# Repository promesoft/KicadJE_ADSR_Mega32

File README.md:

# KicadJE_ADSR_Mega32
Initial ATMega32 board (EU-5 ADSR32)

Second PT2399 reverb (EU-4 Reverb)

Third VCO - based on Format VCO (VCO3)

# Purpose
1 - try out ATMega 32 for digital applications with more IO

2 - PT2399 2nd revision

3 - Formant VCO modification 3rd rev

# Status - delivered
## Initial 
| Stage  | Detail | Status |
| ------------- | ------------- | ------------- |
| create material  | sch/pcb | OK  |
| | gerber | OK |
| production  |   | OK |
|  | produced | OK |
|  | delivered | OK |

## Preliminary validation
| Test  | Detail | Status |
| ------------- | ------------- | ------------- |
| Initial Inspection | | OK |
| Initial Technical Test | ADSR | ICSP:ok - Serial: no success - LED: OK - POT:no success|
| Initial Technical Test | Reverb | OK |
| Initial Technical Test | VCO3 | OK |
| Initial Product Test | ADSR | ADC not working due to GND conn to Aref |
| Initial Product Test | Reverb | Works nicely (tested with 5V from 16pin Doepfer|
| Initial Product Test | VCO3 | Working - output and "sine" - Square not working - UMX1 works nicely as CV - FM works - LFO works - POT's reversed... |

## Secondary validation
| Test  | Detail | Status |
| ------------- | ------------- |------------- |
| Product Test |  |  |
| Product Test |  |  |
| Product Test | VCO | Square not working|
| Quality | | |
| Quality | | |
| Quality | VCO3 | Range from 20Hz |
| Long Term Product Test |  |  |
| Long Term Product Test |  |  |
| Long Term Product Test |  |  |
| Power Draw |  | 
| Power Draw |  | 
| Power Draw | VCO3 | +5V 1mA, +12V 7mA, -12V 6mA 

## Errata
### Errata - VCO3
1 - ALL pots are reversed
### Errata - ADSR Mega32
1 - ADC not working due to GND conn to Aref - fix by bending leg so it does not get soldered

## Issues and Notes
### VCO 3
1 - C104 needs to be bigger (tried w 20uf that worked nicely)

2 - Square circuit not working

3 - Unsure of trigger feature

4 - ALL pots are reversed

5 - Consider adding LED

# Pictures

## VCO3

## Reverb

# Inspiration from 
https://github.com/promesoft/KicadJE_EffectsUnit1

https://github.com/promesoft/ArduinoJE_ADSR

https://github.com/promesoft/KicadFormantVCO

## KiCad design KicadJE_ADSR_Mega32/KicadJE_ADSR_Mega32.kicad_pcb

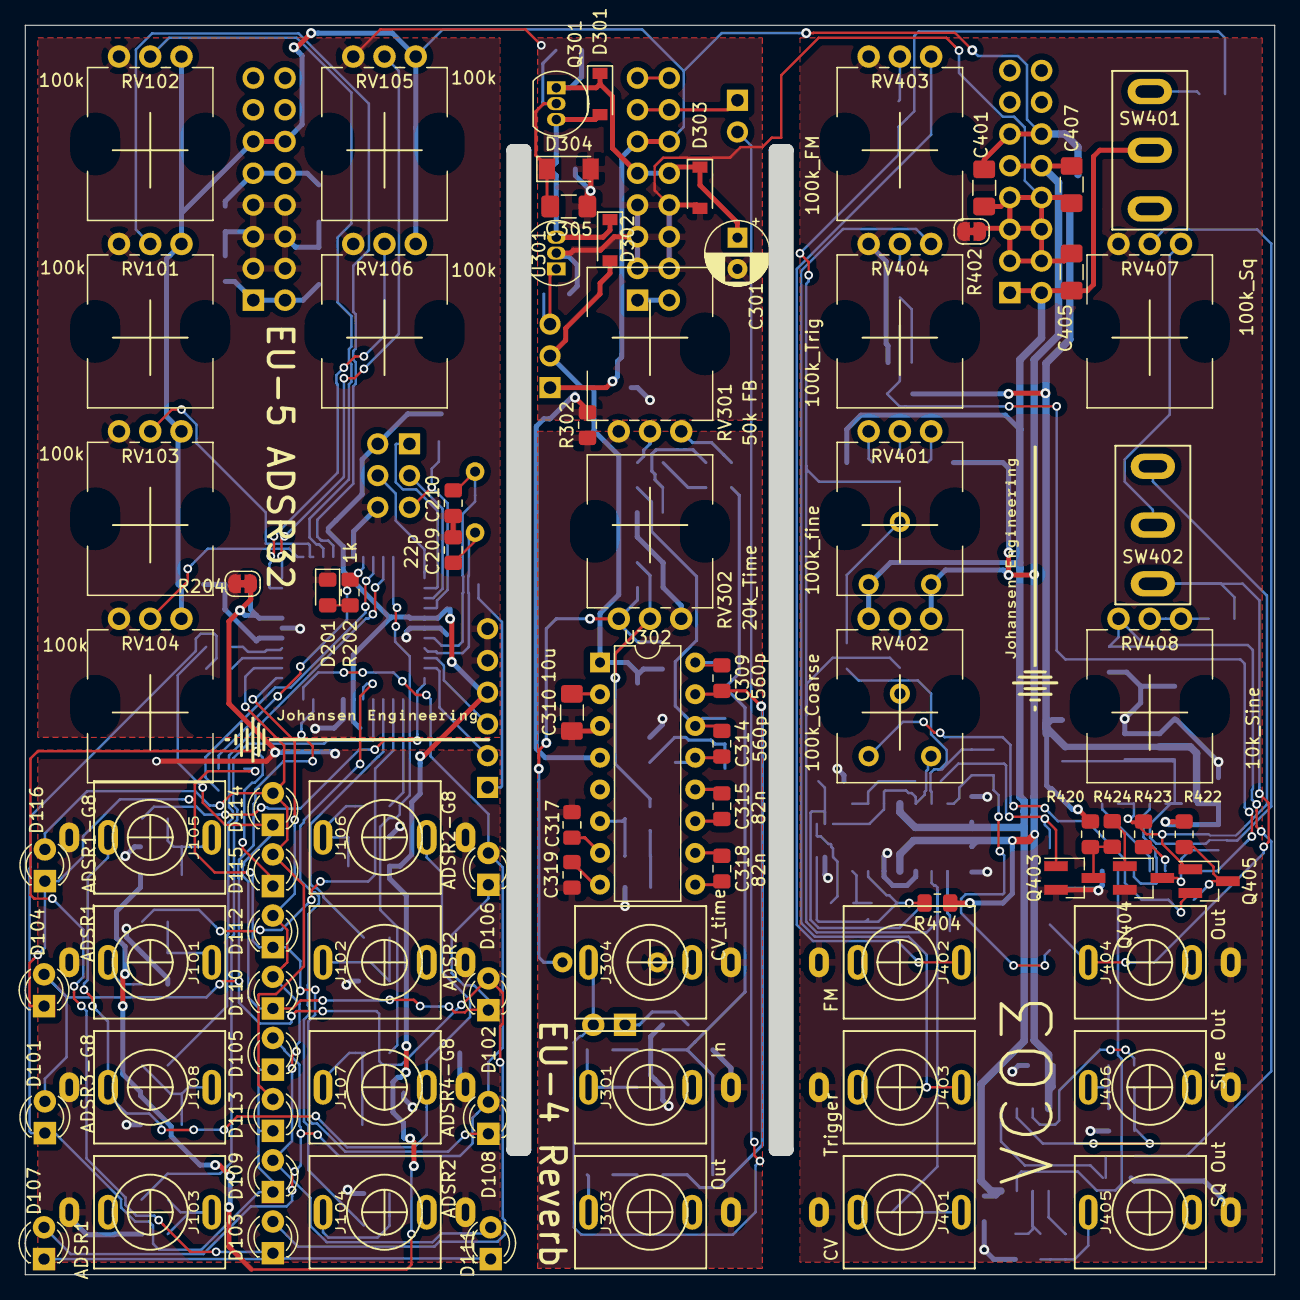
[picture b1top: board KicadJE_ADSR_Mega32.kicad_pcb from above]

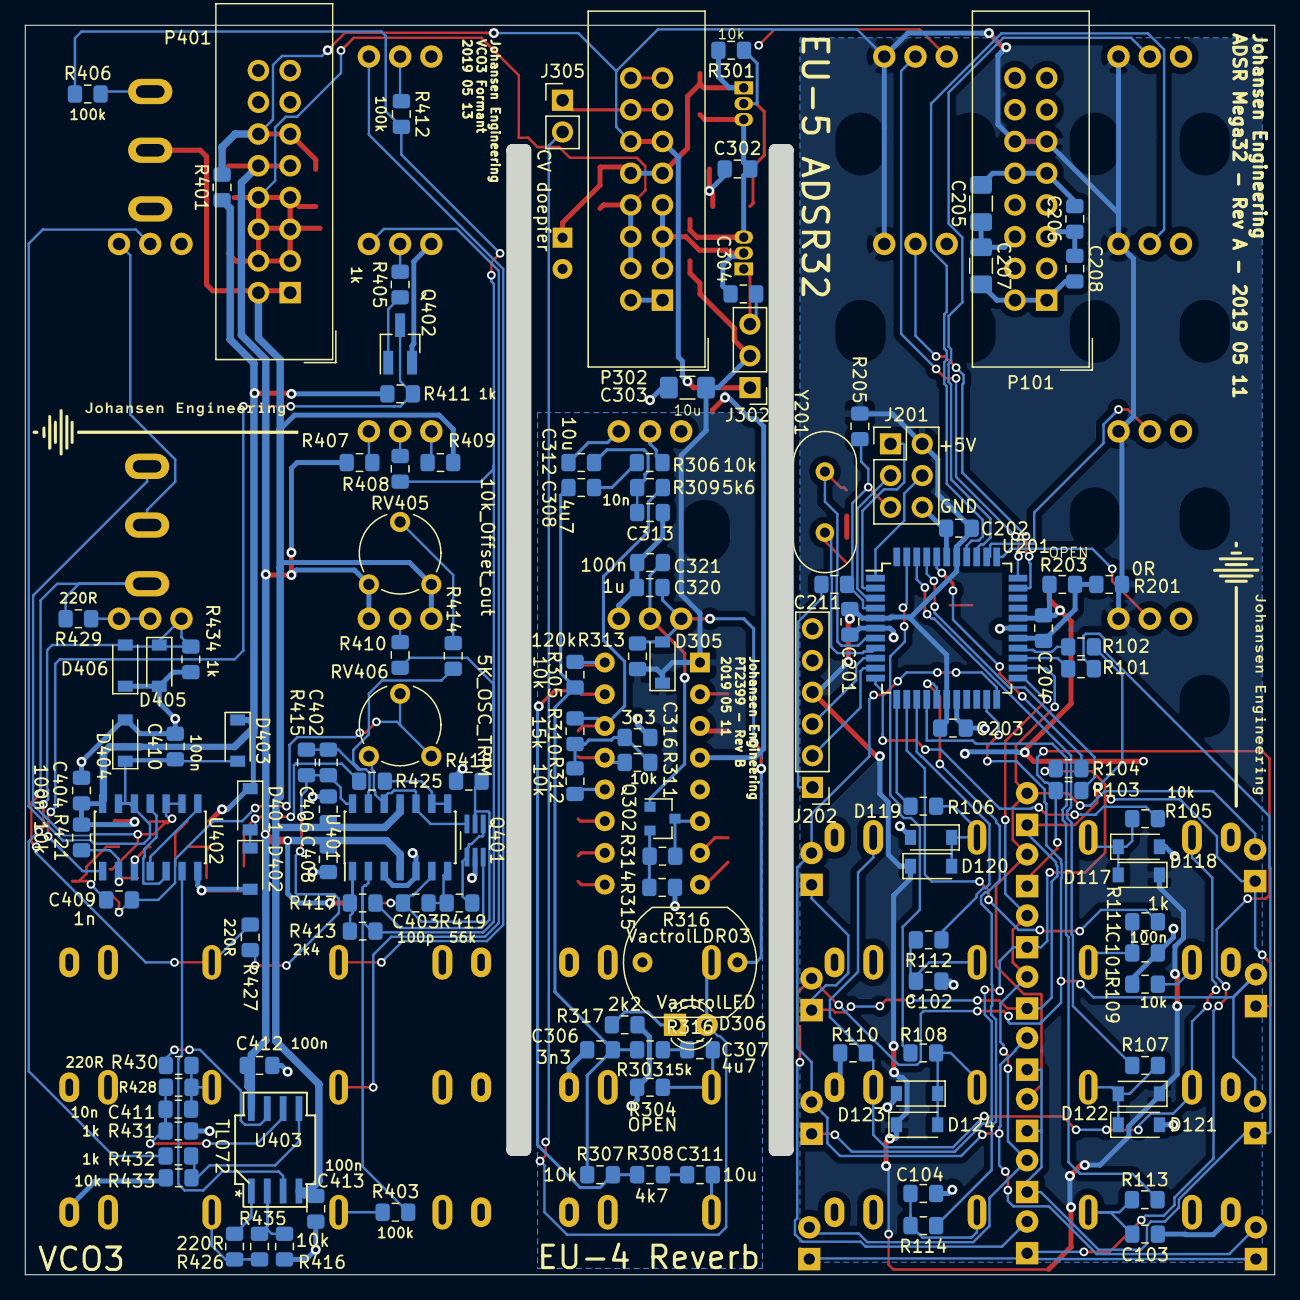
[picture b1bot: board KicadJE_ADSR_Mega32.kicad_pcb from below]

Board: 2 copper layers, 100.0 x 100.0 mm, 213 parts (130 on the bottom side), 132 nets.

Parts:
C101, C103, C201, C202, C203, C204, C206, C208, C211, C302, C304, C317, C319, C321, C404, C406, C408, C410, C412, C413: 100n; C_0805_2012Metric_Pad1.15x1.40mm_HandSolder
C102, C104, C320: 1u; C_0805_2012Metric_Pad1.15x1.40mm_HandSolder
C205, C207: 100n; C_1206_3216Metric_Pad1.42x1.75mm_HandSolder
C209, C210: 22p; C_0805_2012Metric_Pad1.15x1.40mm_HandSolder
C301: 100uF 16v; CP_Radial_D5.0mm_P2.50mm
C303, C305, C310: 10u; C_1206_3216Metric_Pad1.42x1.75mm_HandSolder
C306, C316: 3n3; C_0805_2012Metric_Pad1.15x1.40mm_HandSolder
C307, C308: 4u7; C_0805_2012Metric_Pad1.15x1.40mm_HandSolder
C309, C314: 560p; C_0805_2012Metric_Pad1.15x1.40mm_HandSolder
C311, C312: 10u; C_0805_2012Metric_Pad1.15x1.40mm_HandSolder
C313, C411: 10n; C_0805_2012Metric_Pad1.15x1.40mm_HandSolder
C315, C318: 82n; C_0805_2012Metric_Pad1.15x1.40mm_HandSolder
C401, C405, C407: 1u; C_1206_3216Metric_Pad1.42x1.75mm_HandSolder
C402: 12p; C_0805_2012Metric_Pad1.15x1.40mm_HandSolder
C403: 100p; C_0805_2012Metric_Pad1.15x1.40mm_HandSolder
C409: 1n; C_0805_2012Metric_Pad1.15x1.40mm_HandSolder
D101, D102, D103, D104, D105, D106, D107, D108, D109, D110, D111, D112, D113, D114, D115, D116: LED; LED_D3.0mm
D117, D118, D119, D120, D121, D122, D123, D124, D301, D302, D303, D305: 1N1007; D_SOD-123
D201: LED; LED_0805_2012Metric_Pad1.15x1.40mm_HandSolder
D304: 7v5; D_MiniMELF
D306: VactrolLED; LED_D3.0mm
D401, D402, D403, D404, D405, D406: 1N4148; D_SOD-123
J101, J103: ADSR1; PJ301SM
J102, J104: ADSR2; PJ301SM
J105: ADSR1-G8; PJ301SM
J106: ADSR2-G8; PJ301SM
J107: ADSR4-G8; PJ301SM
J108: ADSR3-G8; PJ301SM
J201: AVR-ISP-6; PinHeader_2x03_P2.54mm_Vertical
J202: UART; PinHeader_1x06_P2.54mm_Vertical
J301: In; PJ301SM
J302: +5V reg/doepfer; PinHeader_1x03_P2.54mm_Vertical
J303, J404: Out; PJ301SM
J304: CV_time; PJ301SM
J305: CV doepfer; PinHeader_1x02_P2.54mm_Vertical
J401: CV; PJ301SM
J402: FM; PJ301SM
J403: Trigger; PJ301SM
J405: SQ Out; PJ301SM
J406: Sine Out; PJ301SM
P101, P302, P401: Doepfer_Power_16pin; IDC-Header_2x08_Pitch2.54mm_Straight
Q301: BC337; TO-92_Inline
Q302: PZT2222A; SOT-23
Q401: UMX1N; SOT-363_SC-70-6_Handsoldering
Q402, Q403, Q404, Q405: MMBT2222A; SOT-23_Handsoldering
R101, R103, R414: 100R; R_0805_2012Metric_Pad1.15x1.40mm_HandSolder
R102, R104: 100r; R_0805_2012Metric_Pad1.15x1.40mm_HandSolder
R105, R106, R107, R108, R109, R110, R112, R114, R205, R301, R305, R306, R307, R311, R312, R416, R420, R421, R422, R428, R433, R435: 10k; R_0805_2012Metric_Pad1.15x1.40mm_HandSolder
R111, R113, R202, R405, R411, R424, R425, R431, R432, R434: 1k; R_0805_2012Metric_Pad1.15x1.40mm_HandSolder
R201, R302, R401: 0R; R_0805_2012Metric_Pad1.15x1.40mm_HandSolder
R203, R304: OPEN; R_0805_2012Metric_Pad1.15x1.40mm_HandSolder
R204, R402: 0R; SolderJumper-2_P1.3mm_Bridged_RoundedPad1.0x1.5mm
R303, R310: 15k; R_0805_2012Metric_Pad1.15x1.40mm_HandSolder
R308, R415: 4k7; R_0805_2012Metric_Pad1.15x1.40mm_HandSolder
R309: 5k6; R_0805_2012Metric_Pad1.15x1.40mm_HandSolder
R313: 120k; R_0805_2012Metric_Pad1.15x1.40mm_HandSolder
R314: 22k; R_0805_2012Metric_Pad1.15x1.40mm_HandSolder
R315: 150R; R_0805_2012Metric_Pad1.15x1.40mm_HandSolder
R316: VactrolLDR03; R_LDR_10x8.5mm_P7.6mm_Vertical
R317: 2k2; R_0805_2012Metric_Pad1.15x1.40mm_HandSolder
R403, R406, R407, R408, R409, R410, R412: 100k; R_0805_2012Metric_Pad1.15x1.40mm_HandSolder
R404: 1M; R_0805_2012Metric_Pad1.15x1.40mm_HandSolder
R413: 2k4; R_0805_2012Metric_Pad1.15x1.40mm_HandSolder
R417: 82R; R_0805_2012Metric_Pad1.15x1.40mm_HandSolder
R418: 910R; R_0805_2012Metric_Pad1.15x1.40mm_HandSolder
R419: 56k; R_0805_2012Metric_Pad1.15x1.40mm_HandSolder
R423, R426, R427, R429, R430: 220R; R_0805_2012Metric_Pad1.15x1.40mm_HandSolder
RV101, RV102, RV103, RV104, RV105, RV106: 100k; Potentiometer_China_RK09_Single_Vertical_AJ
RV301: 50k FB; Potentiometer_China_RK09_Single_Vertical_AJ
RV302: 20k_Time; Potentiometer_China_RK09_Single_Vertical_AJ
RV401: 100k_fine; Potentiometer_China_RK09_Single_Vertical_AJ
RV402: 100k_Coarse; Potentiometer_China_RK09_Single_Vertical_AJ
RV403: 100k_FM; Potentiometer_China_RK09_Single_Vertical_AJ
RV404: 100k_Trig; Potentiometer_China_RK09_Single_Vertical_AJ
RV405: 10k_Offset_out; Potentiometer_Piher_PT-6-V_Vertical
RV406: 5K_OSC_TRIM; Potentiometer_Piher_PT-6-V_Vertical
RV407: 100k_Sq; Potentiometer_China_RK09_Single_Vertical_AJ
RV408: 10k_Sine; Potentiometer_China_RK09_Single_Vertical_AJ
SW401: LFO; SP1MS1
SW402: SQ_Source; SP1MS1
U201: ATmega32A-AU; TQFP-44_10x10mm_P0.8mm
U301: L78L05_TO92; TO-92_Inline
U302: PT2399; DIP-16_W7.62mm
U401: TL074; SOIC-14_3.9x8.7mm_P1.27mm
U402: 74HC00; SOIC-14_3.9x8.7mm_P1.27mm
U403: TL072; AJ_SO-8_5.3x6.2mm_P1.27mm
Y201: 16MHz; Crystal_HC49-U_Vertical

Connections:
0_LED: R104.1, R202.2, U201.40
1: R103.1, U201.41
2_INT2: R107.1, U201.42
3_PWM: R108.1, U201.43
5Vreg: C304.2, J302.3, U301.1
5_MOSI: J201.4, U201.1
6_MISO: J201.1, U201.2
7_SCK: J201.3, U201.3
8_Rx: J202.3, U201.9
9_Tx: J202.2, U201.10
10_INT0: R105.1, U201.11
11_INT1: R106.1, U201.12
12_PWM: R111.1, U201.13
13_PWM: R112.1, U201.14
14_PWM: R113.1, U201.15
15_PWM: R114.1, U201.16
18: D101.2, D102.2, D103.2, D104.2, U201.21
19: D105.2, D106.2, D107.2, D108.2, U201.22
20: D109.2, D110.2, D111.2, D112.2, U201.23
21: D113.2, D114.2, D115.2, D116.2, U201.24
22: R101.1, U201.25
23: R102.1, U201.26
24_A0: RV101.2, U201.37
25_A1: RV102.2, U201.36
26_A2: RV103.2, U201.35
27_A3: RV104.2, U201.34
28_A4: RV105.2, U201.33
29_A5: RV106.2, U201.32
+5V: C201.2, C202.2, C203.2, C401.2, D117.1, D119.1, D121.1, D123.1, J201.2, J202.4, J302.1, P101.11, P101.12, P302.11, P302.12, P401.11, P401.12, R201.2, R205.1, R401.2, RV101.3, RV102.3, RV103.3, RV104.3, RV105.3, RV106.3, U201.5, U201.17, U201.38
+5VA: C204.2, C303.2, C404.2, D302.2, D305.1, D401.1, D403.1, J302.2, R201.1, R203.1, R313.2, R401.1, R411.2, R420.2, R421.2, R422.2, U201.27, U302.1, U402.14
+12V: C205.2, C206.2, C407.2, C408.2, C412.2, P101.9, P101.10, P401.9, P401.10, R404.1, R407.1, RV402.3, RV405.3, U401.4, U403.8
+12Vb: C301.1, D301.1, D303.1, P302.9, P302.10, Q301.1, R301.2
-12V: C207.2, C208.2, C405.2, C406.2, C413.2, P101.1, P101.2, P401.1, P401.2, R409.1, RV402.1, RV405.1, SW401.2, U401.11, U403.4
-12Vb: P302.1, P302.2
/AJ_VCO_Formant/b1: Q401.2, R417.1, R418.2
/AJ_VCO_Formant/c1: C403.1, Q401.6, R404.2, U401.6
/AJ_VCO_Formant/e1: Q401.1, Q401.4, R419.2
/KicadJE-EU1-PT2399_sub/7v5: C302.2, D301.2, D302.1, Q301.3, U301.3
/KicadJE-EU1-PT2399_sub/VCO: Q302.3, R314.2, U302.6
ADSR1: C101.2, J101.T, R111.2
ADSR1-G8: D117.2, D118.1, J105.T, R105.2
ADSR2: C102.2, J102.T, R112.2
ADSR2-G8: D119.2, D120.1, J106.T, R106.2
ADSR3: C103.2, J103.T, R113.2
ADSR3-G8: D121.2, D122.1, J108.T, R107.2
ADSR4: C104.2, J104.T, R114.2
ADSR4-G8: D123.2, D124.1, J107.T, R108.2
CV: D306.2, J304.T, J305.2
CV_B: J305.1, P302.13, P302.14
DelayLine_In: C309.2, R307.2, R308.2, U302.15
GND: C201.1, C202.1, C203.1, C205.1, C206.1, C207.1, C208.1, C209.2, C210.2, C301.2, C302.1, C303.1, C304.1, C305.1, C401.1, C405.1, C407.1, D201.1, D303.2, D304.2, J201.6, J202.5, J202.6, P101.3, P101.4, P101.5, P101.6, P101.7, P101.8, P302.3, P302.4, P302.5, P302.6, P302.7, P302.8, P401.3, P401.4, P401.5, P401.6, P401.7, P401.8, R204.2, R302.2, R402.2, RV101.1, RV102.1, RV103.1, RV104.1, RV105.1, RV106.1, U201.6, U201.18, U201.28, U201.39, U301.2, U302.4
GNDA: C101.1, C102.1, C103.1, C104.1, C204.1, C306.2, C310.1, C313.2, C316.2, C317.1, C319.1, C320.2, C321.1, C404.1, C406.1, C408.1, C410.2, C412.1, C413.1, D118.2, D120.2, D122.2, D124.2, D402.2, D404.2, D405.2, D406.1, J101.S, J102.S, J103.S, J104.S, J105.S, J106.S, J107.S, J108.S, J301.S, J303.S, J304.S, J401.S, J402.S, J403.S, J404.S, J405.S, J406.S, Q401.5, Q402.2, Q403.2, Q404.2, R109.1, R110.2, R203.2, R204.1, R302.1, R304.1, R315.1, R316.2, R317.1, R402.1, R416.1, R418.1, R431.1, R433.1, R434.1, RV301.3, RV302.1, RV403.1, RV404.1, RV407.1, U201.29, U302.3, U401.3, U401.5, U402.7
GateB: P302.15, P302.16
In2399: C307.2, J301.T, R304.2
LFP1-In: C309.1, R305.2, U302.16
LFP2-Out: C314.1, R309.2, R310.2, U302.14
unnamed: C209.1, U201.8, Y201.1
unnamed: C210.1, U201.7, Y201.2
unnamed: C211.2, J202.1
unnamed: C305.2, D304.1, Q301.2, R301.1
unnamed: C306.1, C308.1, R303.2, R305.1, R307.1
unnamed: C307.1, R303.1
unnamed: C308.2, R306.1
unnamed: C310.2, U302.2
unnamed: C311.1, R308.1
unnamed: C312.1, C313.1, R309.1
unnamed: C312.2, RV301.1
unnamed: C314.2, R311.2, U302.13
unnamed: C315.1, R312.2, U302.12
unnamed: C315.2, U302.11
unnamed: C316.1, R310.1, R311.1, R312.1
unnamed: C317.2, U302.7
unnamed: C318.1, U302.10
unnamed: C318.2, U302.9
unnamed: C319.2, U302.8
unnamed: C320.1, D305.2, R313.1, R316.1, RV302.3
unnamed: C321.2, Q302.1, RV302.2
unnamed: C402.1, R414.1, R415.1, U401.13
unnamed: C402.2, R415.2, R427.2, U401.14
unnamed: C403.2, R419.1, U401.7
unnamed: C409.1, Q405.3, R422.1
unnamed: C409.2, Q405.2, RV406.1, RV406.2
unnamed: C410.1, D403.2, D404.1, RV407.2, U402.12, U402.13
unnamed: C411.2, R428.1, R431.2, U403.6
unnamed: D101.1, D105.1, D109.1, D113.1, R101.2
unnamed: D102.1, D106.1, D110.1, D114.1, R102.2
unnamed: D103.1, D107.1, D111.1, D115.1, R103.2
unnamed: D104.1, D108.1, D112.1, D116.1, R104.2
unnamed: D201.2, R202.1
unnamed: D306.1, R317.2
unnamed: D401.2, D402.1, Q403.1, R425.1
unnamed: D405.1, D406.2, R432.1, R434.2, RV408.1
unnamed: J101.TN, R109.2
unnamed: J105.TN, J106.TN, J107.TN, J108.TN, R110.1
unnamed: J401.T, R403.1
unnamed: J402.T, RV403.3
unnamed: J403.T, RV404.3
unnamed: Q302.2, R314.1, R315.2
unnamed: Q402.1, R405.1
unnamed: Q403.3, R420.1, R424.2
unnamed: Q404.1, R424.1
unnamed: Q404.3, R421.1, U402.2
unnamed: R306.2, RV301.2
unnamed: R405.2, RV404.2
unnamed: R406.2, SW401.1
unnamed: R407.2, RV401.3
unnamed: R408.1, RV401.2
unnamed: R409.2, RV401.1
unnamed: R410.1, RV402.2
unnamed: R412.1, RV403.2
unnamed: R413.2, R417.2, U401.1
unnamed: R414.2, RV405.2
unnamed: R416.2, R435.1, U403.2
unnamed: R423.2, U402.3
unnamed: R425.2, U401.8, U401.9
unnamed: R426.2, U403.1
unnamed: R429.1, RV408.2, RV408.3
unnamed: R430.2, U403.7
unnamed: R432.2, R433.2, U403.5
unnamed: RV407.3, SW402.2
unnamed: U402.4, U402.8
unnamed: U402.6, U403.3
unnamed: U402.5, U402.11
Out2399: C311.2, J303.T
VCO_Control: R403.2, R406.1, R408.2, R410.2, R412.2, R413.1, U401.2
VCO_Exp: Q401.3, RV406.3, U401.10, U401.12
VCO_Nand: Q405.1, R423.1, SW402.3, U402.9, U402.10
VCO_Out: J404.T, R427.1, R429.2, SW402.1
VCO_SIN_Out: C411.1, J406.T, R428.2, R430.1
VCO_SQ_Out: J405.T, R426.1, R435.2
VCO_Sync: Q402.3, R411.1, U402.1
reset: C211.1, J201.5, R205.2, U201.4

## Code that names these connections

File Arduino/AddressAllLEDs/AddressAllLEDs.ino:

/***************************************************
 Simple AVR sketch to blink an LED (or similar)
 connected to PB0 (Arduino pin D0)
 Note that the compiled sketch is significally
 smaller that the original Arduino blink sketch.
 A detailed explaination about debugging, port and
 pin definitions can be watched here:
 https://www.youtube.com/watch?v=plJf0r7IcWc
***************************************************/ 


#include <avr/io.h>
#include <util/delay.h>

#define D101row 0b00000100 // ADSR3G8
#define ADSR3G8 0b00000100
#define D102row 0b00000100 // ADSR2
#define ADSR2   0b00000100
#define D103row 0b00000100 // VU 0
#define VU0 0b00000100 //
#define D104row 0b00000100 // ADSR1
#define ADSR1   0b00000100

#define D105row 0b00001000 // VU 3
#define VU3 0b00001000
#define D106row 0b00001000 // ADSR2G8
#define ADSR2G8 0b00001000
#define D107row 0b00001000 // ADSR3
#define ADSR3   0b00001000 
#define D108row 0b00001000 // ADSR4G8
#define ADSR4G8 0b00001000 

#define D109row 0b00010000 // VU 1
#define VU1     0b00010000
#define D110row 0b00010000 // VU 4
#define VU4     0b00010000
#define D111row 0b00010000 // ADSR4
#define ADSR4   0b00010000 
#define D112row 0b00010000 // VU 5
#define VU5     0b00010000

#define D113row 0b00100000 // VU 2
#define VU2     0b00100000 
#define D114row 0b00100000 // VU 7
#define VU7     0b00100000 
#define D115row 0b00100000 // VU 6
#define VU6     0b00100000 
#define D116row 0b00100000 // ADSR1G8
#define ADSR1G8 0b00100000

char col_0_LED = 0x00;
char col_1_LED = 0x00;
char col_2_LED = 0x00;
char col_3_LED = 0x00;
int counter = 0;

int main(void)
{       

  /************************************************ 
   A few different ways to set a pin as output and 
   ignore the rest of the pins. Pick your favorite!
  *************************************************/
//  DDRB |= 0x0F; // XXXXXXXX | 00000001 = XXXXXXX1
//  DDRB |= 0b00000011;
//  PORTB = 0x00;
//  DDRC |= 0xFF; // XXXXXXXX | 00000001 = XXXXXXX1
//  DDRC |= 0b11111100;
//  PORTC = 0x00;
  //DDRB |= _BV(PB0); // Set PB0 as output, ignore the rest
  //DDRB |= (1 << PB0); // Shift the number '1' left 'PB0' times (PB0 = 1)
  DDRB |= (1 << PB0);
  DDRB |= (1 << PB1);

  DDRC |= (1 << PB2);
  DDRC |= (1 << PB3);
  DDRC |= (1 << PB4);
  DDRC |= (1 << PB5);
  DDRC |= (1 << PB6);
  DDRC |= (1 << PB7);

  /************************************************ 
   A few different ways to set a pin as input and 
   ignore the rest of the pins.
  *************************************************/
  //DDRB &= ~0x01; //00000001 -> 11111110 & XXXXXXXX = XXXXXXX0
  //DDRB &= ~_BV(PB0); 
  //DDRB &= ~(1 << PB0);

  // Infinite loop
  while(1)
  {
    /*********************************************** 
     A few different ways to set a pin high and 
     ignore the rest of the pins. 
    ************************************************/
    //PORTB |= 0x01;  // XXXXXXXX | 00000001 = XXXXXXX1
    //PORTB |= _BV(PB0);
    //PORTB |= (1 << PB0);
    //SetPinHigh(&PORTB, 0); 
    
    /*********************************************** 
     A few different ways to set a pin low and 
     ignore the rest of the pins.
    ************************************************/
    //PORTB &= ~0x01;  // 00000001 -> 11111110 & XXXXXXXX = XXXXXXX0
    //PORTB &= ~_BV(PB0);
    //PORTB &= ~(1 << PB0);
    //SetPinLow(&PORTB, 0);

    counter++;
    if (counter >= 100) {
      col_2_LED |= VU0;
      col_3_LED |= ADSR1;
      if (counter >= 200) {
        col_0_LED |= VU1;
        col_3_LED &= ~ADSR1;
        col_3_LED |= ADSR1G8;
        if (counter >= 300) {
          col_0_LED |= VU2;
          col_3_LED &= ~ADSR1G8;
          col_1_LED |= ADSR2;
          if (counter >= 400) {
            col_0_LED |= VU3;
            col_1_LED &= ~ADSR2;
            col_1_LED |= ADSR2G8; 
            if (counter >= 500) {
              col_1_LED |= VU4; 
              col_1_LED &= ~ADSR2G8;
              col_2_LED |= ADSR3; 
              if (counter >= 600) {
                col_3_LED |= VU5; 
                col_2_LED &= ~ADSR3; 
                col_0_LED |= ADSR3G8; 
                if (counter >= 700) {
                  col_2_LED |= VU6; 
                  col_0_LED &= ~ADSR3G8; 
                  col_2_LED |= ADSR4; 
                  if (counter >= 800) {
                    col_1_LED |= VU7; 
                    col_2_LED &= ~ADSR4; 
                    col_3_LED |= ADSR4G8; 
                    if (counter >= 850) {
                      counter = 0;
                      col_0_LED = 0x00;
                      col_1_LED = 0x00;
                      col_2_LED = 0x00;
                      col_3_LED = 0x00;
                    }
                  }
                }
              }
            }
          }
        }
      }
    }

    for (int column = 0; column < 4; column++) {
      _delay_ms(2);
      if (column == 0) {
        SetPinLow(&PORTC, 6); //D22
        PORTC |= col_0_LED;
      }
      else SetPinHigh(&PORTC, 6);
      if (column == 1) {
        SetPinLow(&PORTC, 7); //D23
        PORTC |= col_1_LED;
      }
      else SetPinHigh(&PORTC, 7);
      if (column == 2) {
        SetPinLow(&PORTB, 1); //D1
        PORTC |= col_2_LED;
      }
      else SetPinHigh(&PORTB, 1);
      if (column == 3) {
        SetPinLow(&PORTB, 0); //D0
        PORTC |= col_3_LED;
      }
      else SetPinHigh(&PORTB, 0);

      _delay_ms(1);
      PORTC = 0x00;
    }
  }
  return 0;
}


// Method to set a pin HIGH
void SetPinHigh(volatile byte *port, byte pin)
{
  *port |= (1 << pin); // The number '1' are shifted left 'pin' times
}

// Method to set pin LOW
void SetPinLow(volatile byte *port, byte pin)
{
  *port &= ~(1 << pin); // The number '1' are shifted left 'pin' times
}

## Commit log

2019-04-23 Sch initiated
2019-04-23 ATMega32 minimum
2019-04-24 Annotate ATMega32
2019-04-24 power sch
2019-04-25 Hierarchical + LED Matrix
2019-04-25 Annotation 1
2019-04-26 antilatchup changed PT2399
2019-04-26 L7805 -> 78L05 on PT2399
2019-04-26 PT2399 Delay pot rev
2019-04-27 Vactrol on delay time
2019-04-27 Initial PCB - PT2399
2019-04-27 pwr components place - PT2399
2019-04-27 PT2399 - PWR and VCO placed
2019-04-27 PT2399 routed
2019-04-28 Change LED Matrix pins
2019-04-29 6x Output 3x Gate
2019-04-29 8x Pots to analogue inputs
2019-05-07 Reduce to 8pot and 8jack
2019-05-07 PCB update
2019-05-07 6 pot and added LP for all PWM out
2019-05-07 Fix LED matrix
2019-05-07 Alternative pull down
    Pull down via 10k but connected via TN - so if no input is applied they are connected via Gate input. This enables sync gate
2019-05-10 power routing
2019-05-11 Prior to turning Atmega32
2019-05-11 Atmega rotated
2019-05-11 Update KicadJE_ADSR_Mega32.kicad_pcb
    Power rerouted to Atmega32
2019-05-11 Update KicadJE_ADSR_Mega32.kicad_pcb
    GND fill
2019-05-11 Update KicadJE_ADSR_Mega32.kicad_pcb
    Top section routed initially
2019-05-11 GNDA for all IO
2019-05-11 ATMega32A routed
2019-05-11 labeling
2019-05-11 Logo
2019-05-11 LAbels on PCB - New circuit on sch for VCO
2019-05-11 VCO Input circuit
2019-05-11 pots and jacks placed left...
2019-05-11 VCO oscillator and V to exp
2019-05-11 Core VCO done
2019-05-11 Front components plaecd for VCO
2019-05-12 Sine and Square circuits in sch
2019-05-12 Power done for VCO
2019-05-12 IC Wiring
2019-05-12 Update KicadJE_ADSR_Mega32.kicad_pcb
    interboard +5 / GND
2019-05-12 Potentiometers and Switches
2019-05-12 Square out - and decoupling
2019-05-12 Most of the oscillator
2019-05-12 Oscillator done
2019-05-12 VCO routed
2019-05-13 Label on VCO
2019-05-13 DRC, ERC
2019-05-13 Gerber
2019-05-14 Update fp-info-cache
2019-06-03 Pict
2019-07-01 Arduino Blink
2019-07-01 Arduino array
2019-07-01 LED operational
2019-07-03 All LED's addressable individually
2019-09-20 Reverb Sch
2025-01-01 backup
